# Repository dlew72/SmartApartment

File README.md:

# SmartApartment

ECE Senior Design Project by Danny Lewis, George Long, Roy Thorstensen, and Olivia Kapp.

Android app was built for Samsung Galaxy S10, but should function on any Android device (Android 6.0+). Volley required.

Smart_Hub_Code, Smart_Light_Code, and Smart_Shade_Code folders contain the code and guides for powering the HUZZAH boards.

KiCadProjects contains the schematics for the devices, as well as the PCB designs.

3DPrints contains STL files for various prints that make up enclosures and supporting peices.

See "Final Report.pdf" (coming soon) for more details on this project and its uses.

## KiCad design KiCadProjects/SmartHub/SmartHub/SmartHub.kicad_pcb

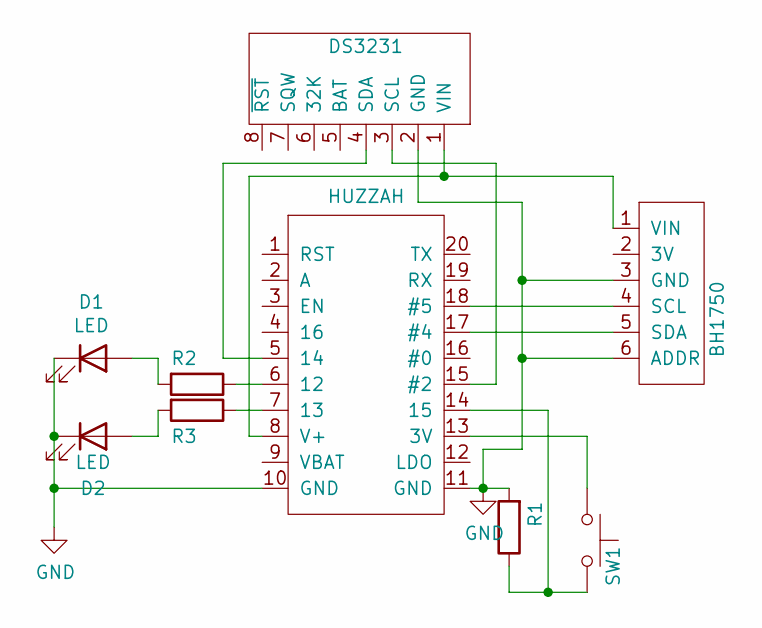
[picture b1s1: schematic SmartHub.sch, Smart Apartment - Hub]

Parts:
D1, D2: LED; LED_D2.0mm_W4.8mm_H2.5mm_FlatTop
R1, R2, R3: R; R_Axial_DIN0207_L6.3mm_D2.5mm_P10.16mm_Horizontal
SW1: SW_Push; R_Axial_DIN0204_L3.6mm_D1.6mm_P5.08mm_Horizontal
U1: DS3231; DS3231_FOOT
U2: BH1750; BH1750_BO_FOOT
u1: HUZZAH; HUZZAH_FOOT

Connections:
GND: D1.1 (K), D2.1 (K), R1.2, U1.2 (GND), U2.3 (GND), U2.6 (ADDR), u1.10 (GND), u1.11 (GND)
unnamed: D1.2 (A), R2.2
unnamed: D2.2 (A), R3.2
unnamed: R1.1, SW1.2, u1.14 (15)
unnamed: R2.1, u1.6 (12)
unnamed: R3.1, u1.7 (13)
unnamed: SW1.1, u1.13 (3V)
unnamed: U1.1 (VIN), U2.1 (VIN), u1.8 (V+)
unnamed: U1.3 (SCL), u1.15 (#2)
unnamed: U1.4 (SDA), u1.5 (14)
unnamed: U2.4 (SCL), u1.18 (#5)
unnamed: U2.5 (SDA), u1.17 (#4)

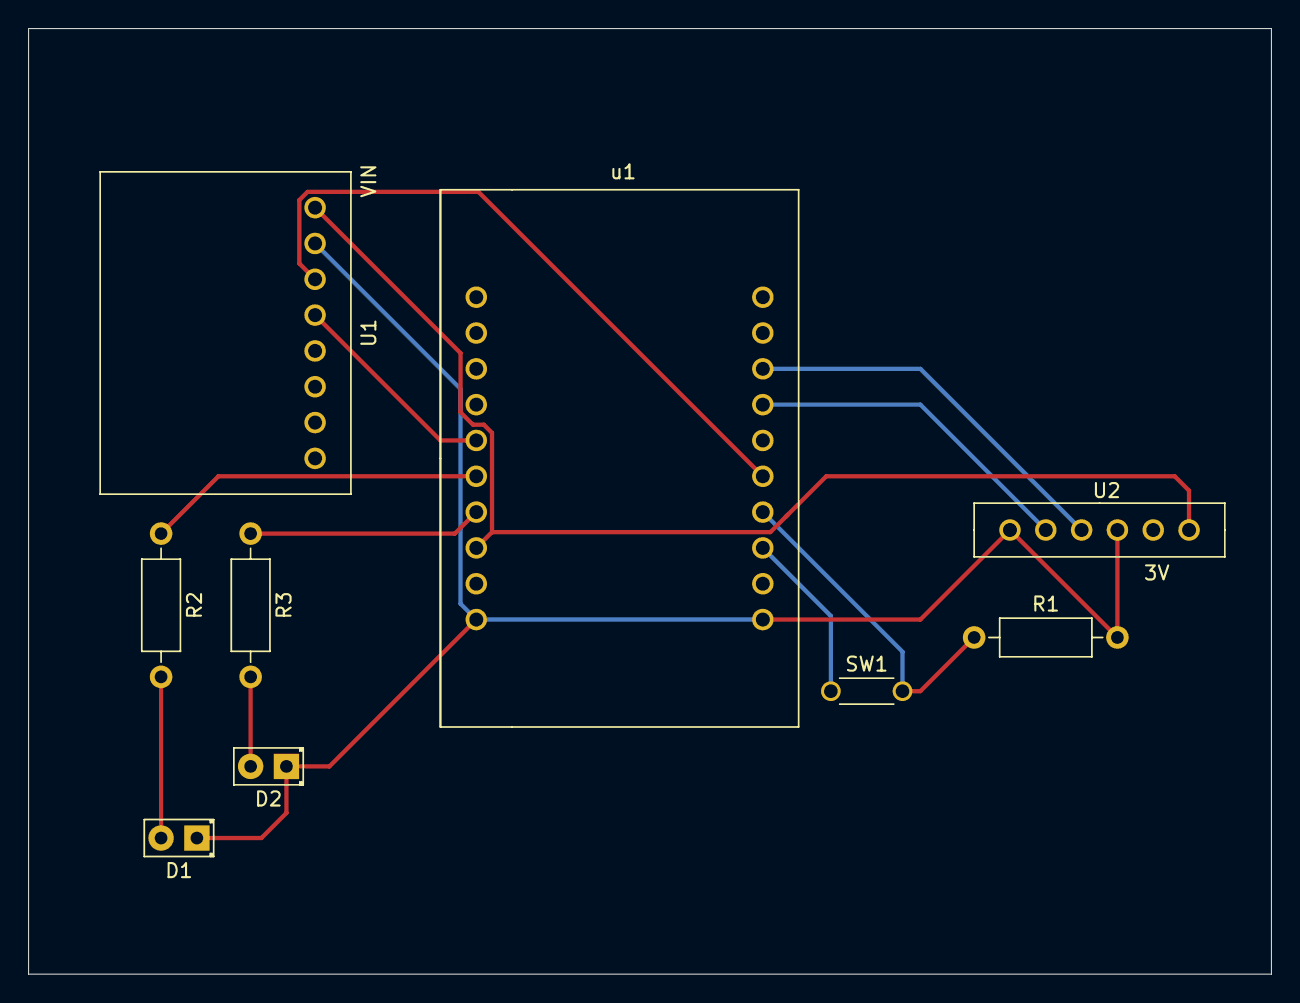
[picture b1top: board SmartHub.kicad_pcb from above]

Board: 2 copper layers, 88.1 x 67.1 mm, 9 parts (0 on the bottom side), 12 nets.

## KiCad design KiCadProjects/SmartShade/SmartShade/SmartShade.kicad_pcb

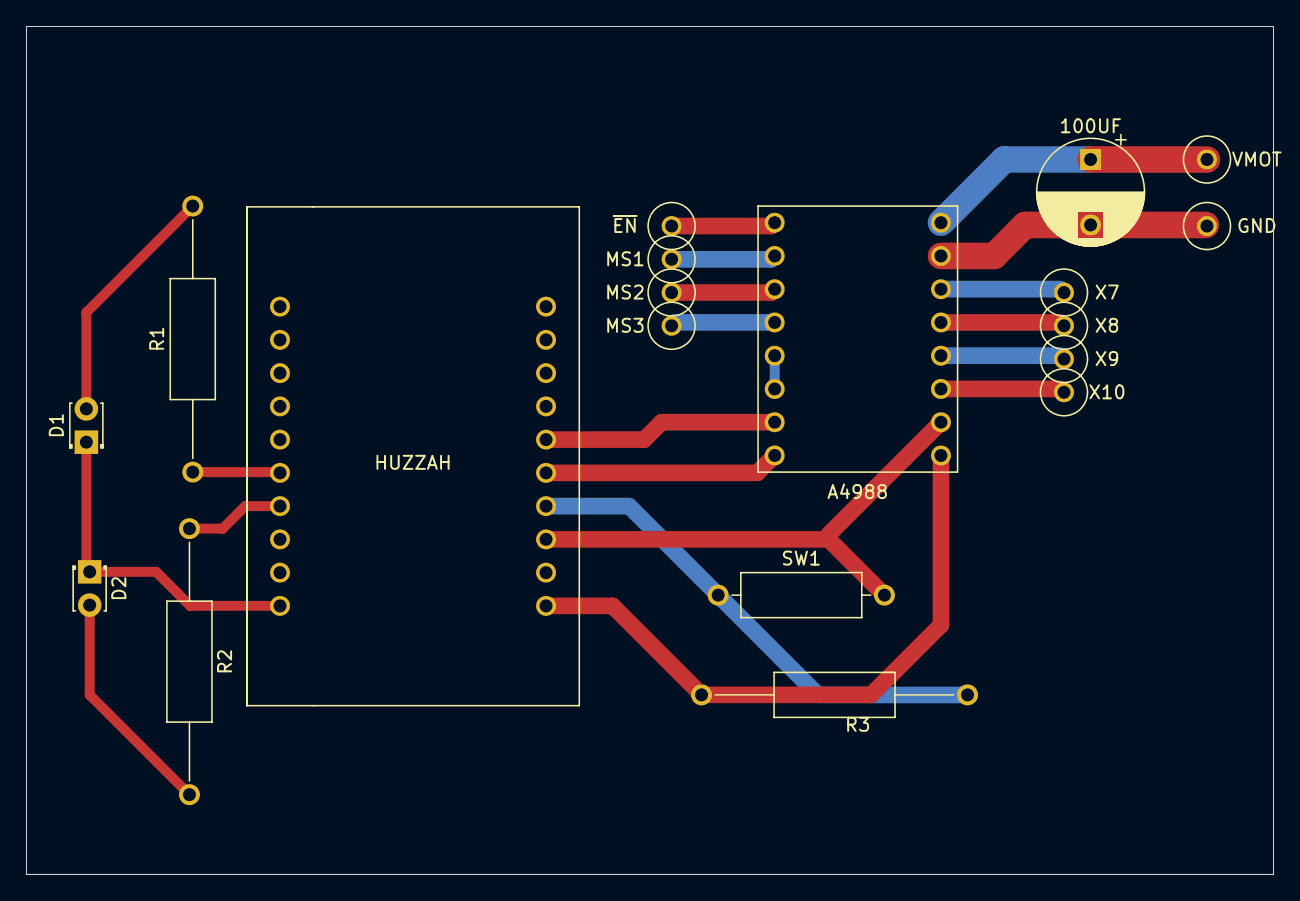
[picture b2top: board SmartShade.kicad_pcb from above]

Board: 2 copper layers, 95.2 x 64.8 mm, 18 parts (0 on the bottom side), 20 nets.

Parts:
100UF: CP; CP_Radial_D8.0mm_P5.00mm
A4988: A4988; a4988_foot
D1, D2: LED; LED_D1.8mm_W3.3mm_H2.4mm
GND: Pad; Pad_FOOT
HUZZAH: HUZZAH; HUZZAH_FOOT
MS1, MS2, MS3: Pad; Pad_FOOT
R1, R2, R3: R; R_Axial_DIN0309_L9.0mm_D3.2mm_P20.32mm_Horizontal
SW1: SW_Push; R_Axial_DIN0309_L9.0mm_D3.2mm_P12.70mm_Horizontal
VMOT: Pad; Pad_FOOT
X7, X8, X9, X10: Pad; Pad_FOOT

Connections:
unnamed: 100UF.1, A4988.16, VMOT.1
unnamed: 100UF.2, A4988.15, GND.1
unnamed: D1.1, D2.1, HUZZAH.10
unnamed: D1.2, R1.2
unnamed: D2.2, R2.2
unnamed: HUZZAH.6, R1.1
unnamed: HUZZAH.7, R2.1
unnamed: A4988.9, HUZZAH.11, R3.1
unnamed: HUZZAH.14, R3.2, SW1.2
unnamed: A4988.10, HUZZAH.13, SW1.1
unnamed: A4988.2, MS1.1
unnamed: A4988.3, MS2.1
unnamed: A4988.4, MS3.1
unnamed: A4988.5, A4988.6
unnamed: A4988.7, HUZZAH.16
unnamed: A4988.8, HUZZAH.15
unnamed: A4988.11, X10.1
unnamed: A4988.12, X9.1
unnamed: A4988.13, X8.1
unnamed: A4988.14, X7.1

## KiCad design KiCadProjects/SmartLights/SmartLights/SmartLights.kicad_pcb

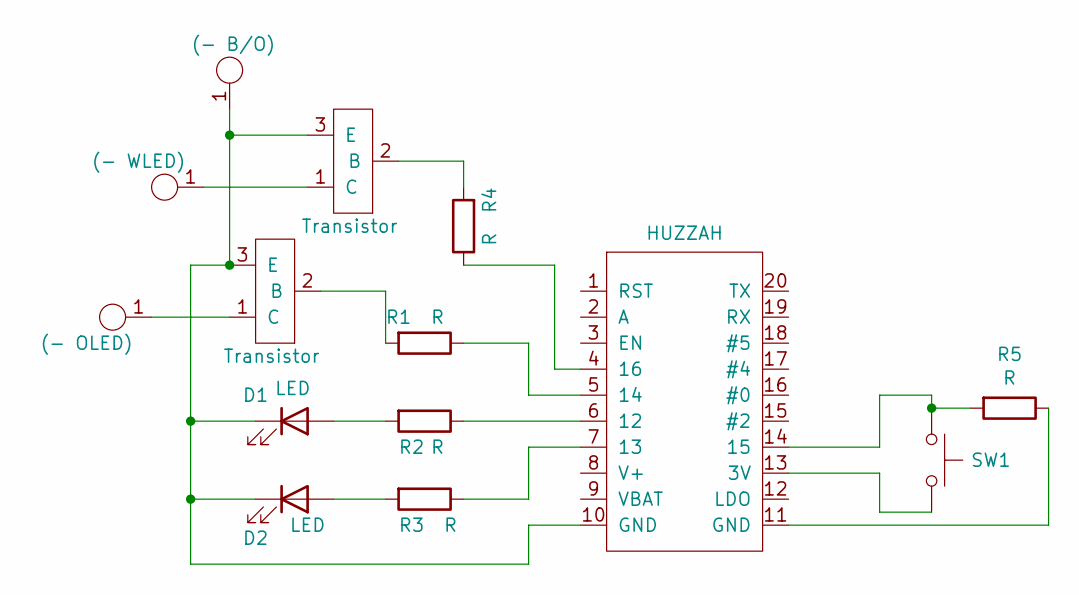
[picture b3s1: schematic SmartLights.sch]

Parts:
D1, D2: LED; LED_D2.0mm_W4.8mm_H2.5mm_FlatTop
Q1, Q2: Transistor; Transistor_FOOT
R1, R2, R3, R4, R5: R; R_Axial_DIN0207_L6.3mm_D2.5mm_P10.16mm_Horizontal
SW1: SW_Push; R_Axial_DIN0207_L6.3mm_D2.5mm_P10.16mm_Horizontal
X1: (- OLED); Pad_FOOT
X2: (- WLED); Pad_FOOT
X3: (- B/O); Pad_FOOT
u1: HUZZAH; HUZZAH_FOOT

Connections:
unnamed: D1.1 (K), D2.1 (K), Q1.3 (E), Q2.3 (E), X3.1, u1.10 (GND)
unnamed: D1.2 (A), R2.2
unnamed: D2.2 (A), R3.2
unnamed: Q1.1 (C), X1.1
unnamed: Q1.2 (B), R1.2
unnamed: Q2.1 (C), X2.1
unnamed: Q2.2 (B), R4.2
unnamed: R1.1, u1.5 (14)
unnamed: R2.1, u1.6 (12)
unnamed: R3.1, u1.7 (13)
unnamed: R4.1, u1.4 (16)
unnamed: R5.1, u1.11 (GND)
unnamed: R5.2, SW1.1, u1.14 (15)
unnamed: SW1.2, u1.13 (3V)

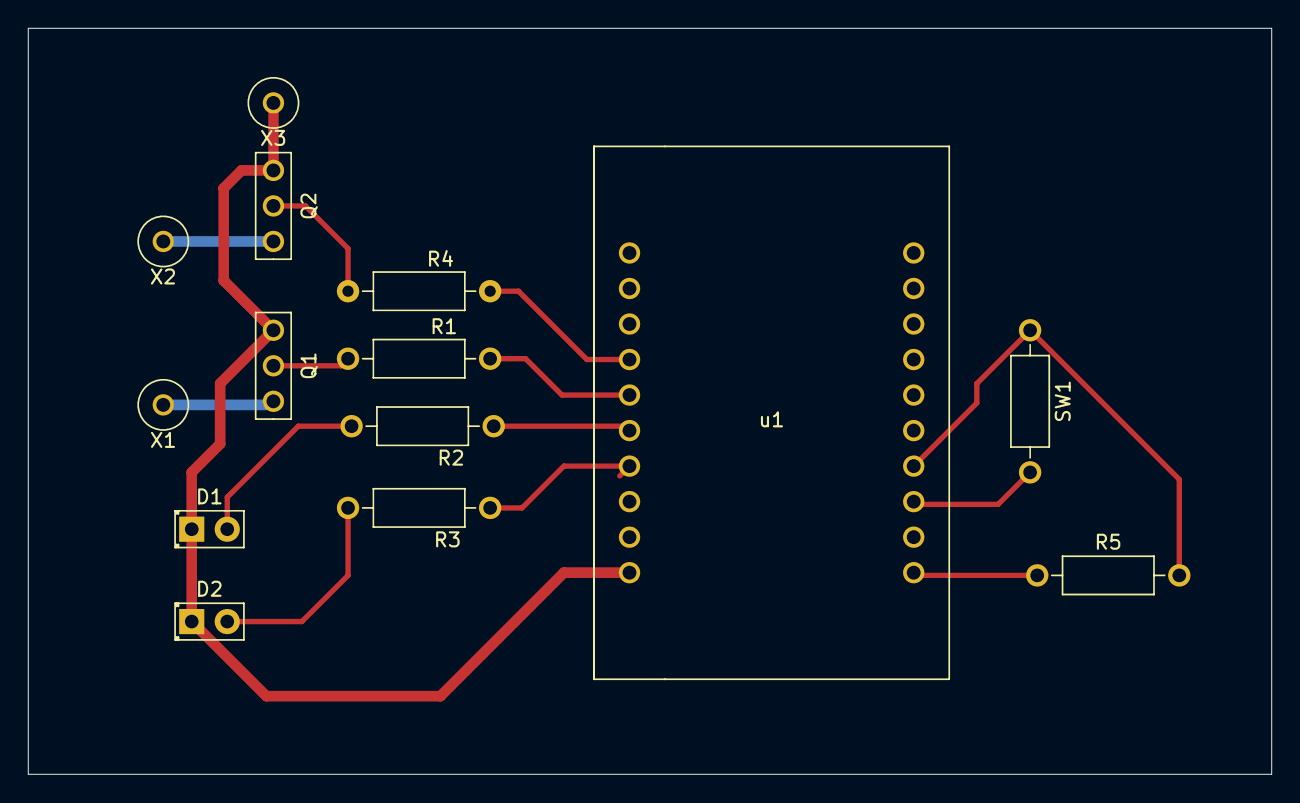
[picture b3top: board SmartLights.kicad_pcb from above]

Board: 2 copper layers, 88.9 x 53.3 mm, 14 parts (0 on the bottom side), 14 nets.

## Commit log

2021-08-09 Initital Commit
2021-08-09 set up splash screen logic
2021-08-22 Implement skeleton setup screens
2021-08-22 Starting dashboard
2021-08-23 dashboard cont.
2021-08-24 good place with dashboard formatting
2021-08-24 light is now dynamic
2021-08-24 patched dynamic light
2021-08-24 add checkConnection logic / flow
2021-08-24 added action bar screens, started settings dash
2021-08-25 format dashboard a little cleaner, slightly more work towards settings dash
2021-08-25 more misc work
2021-08-25 more work
2021-08-26 more misc work 1
2021-08-28 more misc work 2
2021-08-30 dashboard rework (in progress)
2021-08-31 dashboard now looks good on s10 emu and pixel emu
2021-08-31 light settings activity implemented
2021-08-31 shade settings activity implemented
2021-08-31 save progress
2021-09-01 add tabbed activity (scheduler)
2021-09-07 implement action class
2021-09-07 working on scheduler
2021-09-08 working on scheduler -- lights
2021-09-12 major work on new light action screen
2021-09-13 Smart Light actions are now fully creatable and deletable - needs UI formatting though
2021-09-13 made light scheduler look more presentable
2021-09-13 tweaked light scheduler frontend
2021-09-13 AM/PM bug fix
2021-09-13 light scheduler now sorts the displayed actions
2021-09-13 code cleanup
2021-09-13 fixed missing dependency
2021-09-13 added scrolling to light scheduler
2021-09-13 added shade scheduler!
2021-09-14 remove dark mode differences and updated some coloring
2021-09-14 updated setup UI
2021-09-14 minor text tweak
2021-09-14 shade is animated
2021-09-14 add files
2021-09-16 start wifi backend
2021-09-20 start of http smarthub communication
2021-09-26 volley
2021-09-26 sends creds
2021-09-27 now checks if on same network in beginning
2021-09-27 setup flow (hub only) complete
2021-09-29 realtime packet sending test, plus major code writes for all three microcontrollers
2021-09-29 realtime packet sending refine
2021-09-29 remove delay
2021-09-29 clean up packet sending
2021-09-29 Created smart hub guide -- currently includes memory maps
2021-10-03 file restructuring, setup delay
2021-10-08 images
2021-10-19 settings implemented in app interrupts implemented in all devices sync schedule routine begun
2021-10-19 first attempt at sending schedule
2021-10-19 schedule receives, but is not parsed correctly
2021-10-26 schedule received and parsed and stored into memory
2021-10-26 minor documentation fix
2021-10-26 final schedule edits before rtc testing
2021-10-26 final schedule edits before rtc testing real
2021-11-30 major work
2021-11-30 very close
2021-12-01 shade code should be done
2021-12-01 WORKING
2021-12-02 final commit
2021-12-09 Code formatting cleanup
2021-12-10 resolve differences between double light file
2021-12-11 add KiCad files
2021-12-11 add 3D models (stls)
